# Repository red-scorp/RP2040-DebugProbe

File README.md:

```
____________  _____  _____    ___ _____                
| ___ \ ___ \/ __  \|  _  |  /   |  _  |               
| |_/ / |_/ /`' / /'| |/' | / /| | |/' |               
|    /|  __/   / /  |  /| |/ /_| |  /| |               
| |\ \| |    ./ /___\ |_/ /\___  \ |_/ /               
\_| \_\_|    \_____/ \___/     |_/\___/                
______     _                ______          _          
|  _  \   | |               | ___ \        | |         
| | | |___| |__  _   _  __ _| |_/ / __ ___ | |__   ___ 
| | | / _ \ '_ \| | | |/ _` |  __/ '__/ _ \| '_ \ / _ \
| |/ /  __/ |_) | |_| | (_| | |  | | | (_) | |_) |  __/
|___/ \___|_.__/ \__,_|\__, \_|  |_|  \___/|_.__/ \___|
                        __/ |                          
                       |___/                           
```

# RP2040-DebugProbe Project

The **RP2040-DebugProbe** project aims to re-imagine Raspberry Pi Debug Probe.

## RP2040-DebugProbe Board

The **RP2040-DebugProbe** board is a 4-layer design intended to accommodate the popular Raspberry Pi RP2040 MCU with all required component to function identically to Raspberry Pi Debug Probe.

This board features target JTAG connector and PC host USB Type-C connector. It also has a SWD connector and UART connector for the main MCU debugging. The board is pin-compatible with Raspberry Pi Debug Probe and can be used with the same picoprobe SW.

Preview:

You can view the [Schematics in PDF format](doc/RP2040-DebugProbe.pdf) for detailed information.

STEP 3D file is available [with pins](doc/RP2040-DebugProbe.step).

Features:

- Very small form-factor of about 50x25mm (2x1in).
- Raspberry Pi RP2040 MCU as a heart of the board.
- 2x5 1.27mm JTAG connector for programming and debugging.
- 1x8 2.54mm SWD/UART/Power connector for programming and debugging.
- USB Type-C connector for power and communication.
- Several LEDs to indicate power and status.
- 2x5 1.27mm SWD connector and 1x3 2.54mm UART connector for main MCU debugging.
- BOOTSEL button to enter the bootloader mode for flashing new picoprobe SW.
- Pin-compatible with Raspberry Pi Debug Probe.
- Extra TARGET_RESET line connected to GPIO10 for target MCU reset over JTAG.

CAM files, as well as the BOM and CPL files for JLCPCB, are available.

## Version History

### v1.0b1

Initial release for testing purposes.

## Links

- [Raspberry Pi RP2040 information page](https://www.raspberrypi.com/documentation/microcontrollers/rp2040.html).
- [Raspberry Pi Debug Probe information page](https://www.raspberrypi.com/documentation/microcontrollers/debug-probe.html).
- [Picoprobe SW for the board](https://github.com/raspberrypi/picoprobe).

## How to Help

Your contributions as code, resources, or finances are welcome! Please contact me directly via email at andriy.golovnya@gmail.com or through my [GitHub profile](https://github.com/red-scorp).

If you'd like to make a financial contribution, you can donate via [PayPal](http://paypal.me/redscorp) or [Ko-Fi](http://ko-fi.com/redscorp). Your support is greatly appreciated.

Thanks in advance!

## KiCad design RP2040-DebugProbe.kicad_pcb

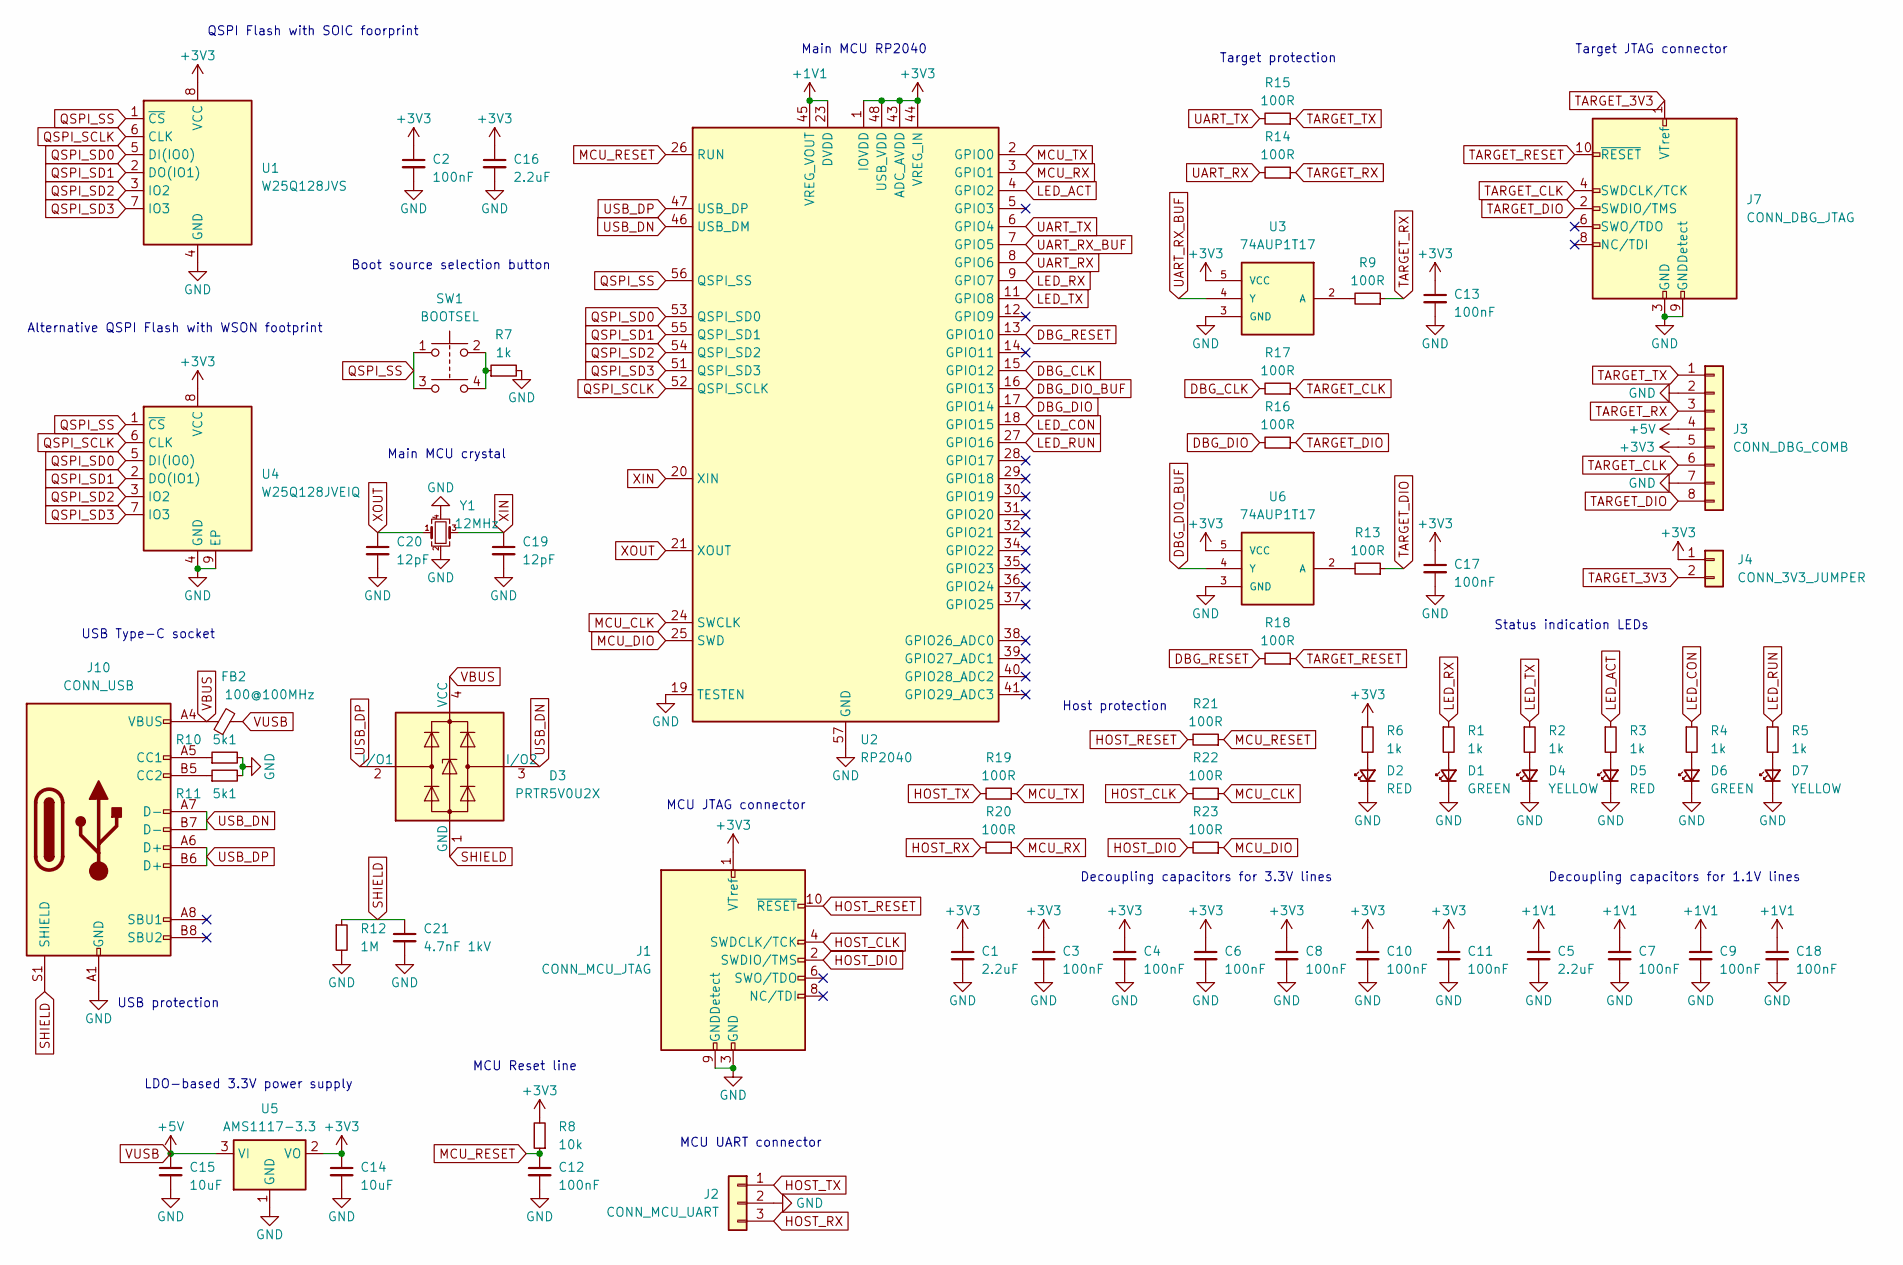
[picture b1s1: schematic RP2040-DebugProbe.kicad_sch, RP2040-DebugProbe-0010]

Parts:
C1, C5, C16: 2.2uF; C_0603_1608Metric
C2, C3, C4, C6, C7, C8, C9, C10, C11, C12, C13, C17, C18: 100nF; C_0402_1005Metric
C14, C15: 10uF; C_0805_2012Metric
C19, C20: 12pF; C_0402_1005Metric
C21: 4.7nF 1kV; C_1206_3216Metric
D1, D6: GREEN; LED_0603_1608Metric
D2, D5: RED; LED_0603_1608Metric
D3: PRTR5V0U2X; SOT-143
D4, D7: YELLOW; LED_0603_1608Metric
FB2: 100@100MHz; L_0805_2012Metric
J1: CONN_MCU_JTAG; PinHeader_2x05_P1.27mm_Vertical
J2: CONN_MCU_UART; PinHeader_1x03_P2.54mm_Vertical
J3: CONN_DBG_COMB; PinHeader_1x08_P2.54mm_Vertical
J4: CONN_3V3_JUMPER; PinHeader_1x02_P2.54mm_Vertical
J7: CONN_DBG_JTAG; PinHeader_2x05_P1.27mm_Vertical
J10: CONN_USB; USB_C_Receptacle_HRO_TYPE-C-31-M-12
R1, R2, R3, R4, R5, R6, R7: 1k; R_0402_1005Metric
R8: 10k; R_0402_1005Metric
R9, R13, R14, R15, R16, R17, R18, R19, R20, R21, R22, R23: 100R; R_0402_1005Metric
R10, R11: 5k1; R_0402_1005Metric
R12: 1M; R_0603_1608Metric
SW1: BOOTSEL; Button_Tact_Sqkg
U1: W25Q128JVS; SOIC-8_5.23x5.23mm_P1.27mm
U2: RP2040; QFN-56-1EP_7x7mm_P0.4mm_EP3.2x3.2mm
U3, U6: 74AUP1T17; SOT-353_SC-70-5
U4: W25Q128JVEIQ; WSON-8-1EP_6x5mm_P1.27mm_EP3.4x4.3mm
U5: AMS1117-3.3; SOT-223-3_TabPin2
Y1: 12MHz; Crystal_SMD_3225-4Pin_3.2x2.5mm

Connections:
+1V1: C5.1, C7.1, C9.1, C18.1, U2.23 (DVDD), U2.45 (VREG_VOUT), U2.50 (DVDD)
+3V3: C1.1, C2.1, C3.1, C4.1, C6.1, C8.1, C10.1, C11.1, C13.1, C14.1, C16.1, C17.1, J1.1 (VTref), J3.5, J4.1, R6.1, R8.2, U1.8 (VCC), U2.1 (IOVDD), U2.10 (IOVDD), U2.22 (IOVDD), U2.33 (IOVDD), U2.42 (IOVDD), U2.43 (ADC_AVDD), U2.44 (VREG_IN), U2.48 (USB_VDD), U2.49 (IOVDD), U3.5 (VCC), U4.8 (VCC), U5.2 (VO), U6.5 (VCC)
DBG_CLK: R17.2, U2.15 (GPIO12)
DBG_DIO: R16.2, U2.17 (GPIO14)
DBG_DIO_BUF: U2.16 (GPIO13), U6.4 (Y)
DBG_RESET: R18.2, U2.13 (GPIO10)
GND: C1.2, C2.2, C3.2, C4.2, C5.2, C6.2, C7.2, C8.2, C9.2, C10.2, C11.2, C12.2, C13.2, C14.2, C15.2, C16.2, C17.2, C18.2, C19.2, C20.2, C21.2, D1.1 (K), D2.1 (K), D4.1 (K), D5.1 (K), D6.1 (K), D7.1 (K), J1.3 (GND), J1.5 (GND), J1.9 (GNDDetect), J2.2, J3.2, J3.7, J7.3 (GND), J7.5 (GND), J7.9 (GNDDetect), J10.A1 (GND), J10.A12 (GND), J10.B1 (GND), J10.B12 (GND), R7.2, R10.2, R11.2, R12.2, U1.4 (GND), U2.19 (TESTEN), U2.57 (GND), U3.3 (GND), U4.4 (GND), U4.9 (EP), U5.1 (GND), U6.3 (GND), Y1.2, Y1.4
HOST_CLK: J1.4 (SWDCLK/TCK), R22.2
HOST_DIO: J1.2 (SWDIO/TMS), R23.2
HOST_RESET: J1.10 (~RESET), R21.2
HOST_RX: J2.3, R20.2
HOST_TX: J2.1, R19.2
LED_ACT: R3.1, U2.4 (GPIO2)
LED_CON: R4.1, U2.18 (GPIO15)
LED_RUN: R5.1, U2.27 (GPIO16)
LED_RX: R1.1, U2.9 (GPIO7)
LED_TX: R2.1, U2.11 (GPIO8)
MCU_CLK: R22.1, U2.24 (SWCLK)
MCU_DIO: R23.1, U2.25 (SWD)
MCU_RESET: C12.1, R8.1, R21.1, U2.26 (RUN)
MCU_RX: R20.1, U2.3 (GPIO1)
MCU_TX: R19.1, U2.2 (GPIO0)
unnamed: D1.2 (A), R1.2
unnamed: D2.2 (A), R6.2
unnamed: D4.2 (A), R2.2
unnamed: D5.2 (A), R3.2
unnamed: D6.2 (A), R4.2
unnamed: D7.2 (A), R5.2
unnamed: J10.A5 (CC1), R10.1
unnamed: J10.B5 (CC2), R11.1
unnamed: R7.1, SW1.2, SW1.4
unnamed: R9.2, U3.2 (A)
unnamed: R13.2, U6.2 (A)
QSPI_SCLK: U1.6 (CLK), U2.52 (QSPI_SCLK), U4.6 (CLK)
QSPI_SD0: U1.5 (DI(IO0)), U2.53 (QSPI_SD0), U4.5 (DI(IO0))
QSPI_SD1: U1.2 (DO(IO1)), U2.55 (QSPI_SD1), U4.2 (DO(IO1))
QSPI_SD2: U1.3 (IO2), U2.54 (QSPI_SD2), U4.3 (IO2)
QSPI_SD3: U1.7 (IO3), U2.51 (QSPI_SD3), U4.7 (IO3)
QSPI_SS: SW1.1, SW1.3, U1.1 (~CS), U2.56 (QSPI_SS), U4.1 (~CS)
SHIELD: C21.1, D3.1 (GND), J10.S1 (SHIELD), R12.1
TARGET_3V3: J4.2, J7.1 (VTref)
TARGET_CLK: J3.6, J7.4 (SWDCLK/TCK), R17.1
TARGET_DIO: J3.8, J7.2 (SWDIO/TMS), R13.1, R16.1
TARGET_RESET: J7.10 (~RESET), R18.1
TARGET_RX: J3.3, R9.1, R14.1
TARGET_TX: J3.1, R15.1
UART_RX: R14.2, U2.8 (GPIO6)
UART_RX_BUF: U2.7 (GPIO5), U3.4 (Y)
UART_TX: R15.2, U2.6 (GPIO4)
USB_DN: D3.3 (I/O2), J10.A7 (D-), J10.B7 (D-), U2.46 (USB_DM)
USB_DP: D3.2 (I/O1), J10.A6 (D+), J10.B6 (D+), U2.47 (USB_DP)
VBUS: D3.4 (VCC), FB2.1, J10.A4 (VBUS), J10.A9 (VBUS), J10.B4 (VBUS), J10.B9 (VBUS)
VUSB: C15.1, FB2.2, J3.4, U5.3 (VI)
XIN: C19.1, U2.20 (XIN), Y1.3
XOUT: C20.1, U2.21 (XOUT), Y1.1

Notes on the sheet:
USB protection
Alternative QSPI Flash with WSON footprint
Main MCU RP2040
Status indication LEDs
MCU JTAG connector
Decoupling capacitors for 3.3V lines
Main MCU crystal
Decoupling capacitors for 1.1V lines
Target protection
Target JTAG connector
USB Type-C socket
Host protection
MCU UART connector
Boot source selection button
LDO-based 3.3V power supply
MCU Reset line
QSPI Flash with SOIC foorprint

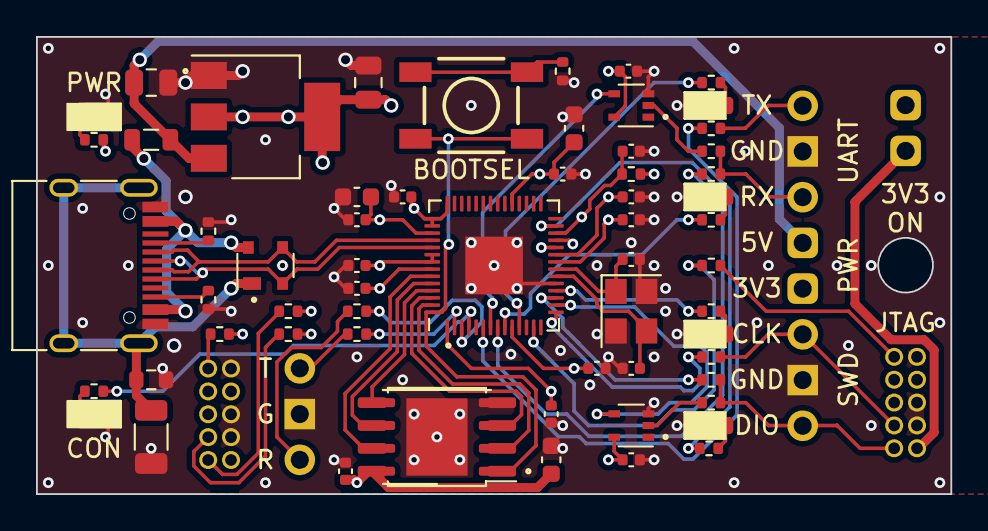
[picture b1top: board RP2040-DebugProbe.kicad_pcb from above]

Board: 4 copper layers, 50.8 x 25.4 mm, 66 parts (0 on the bottom side), 55 nets.

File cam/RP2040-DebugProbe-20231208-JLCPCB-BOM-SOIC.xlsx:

Qty | Designator | Footprint | JLCPCB Part# | Comment
12 | R13,R19,R23,R15,R16,R22,R18,R17,R21,R9,R20,R14 | 0402 | C25076 | 100R
2 | D7,D4 | 0603 | C72038 | YELLOW
13 | C4,C11,C9,C3,C17,C7,C12,C13,C18,C2,C6,C10,C8 | 0402 | C1525 | 100nF
3 | C5,C1,C16 | 0603 | C1604 | 2.2uF
1 | FB2 | 0805 | C1015 | GZ2012D101TF
2 | U3,U6 | SC-70-5 | C2652100 | 74AUP1T17
2 | D2,D5 | 0603 | C2286 | RED
2 | R11,R10 | 0402 | C25905 | 5k1
1 | J1 | SMD,P=1.27mm | C2935953 | CONN_MCU_JTAG
2 | C20,C19 | 0402 | C1547 | 12pF
1 | U2 | LQFN-56(7x7) | C2040 | RP2040
7 | R3,R7,R5,R1,R6,R4,R2 | 0402 | C11702 | 1k
1 | J4 | Plugin,P=2.54mm | C2685154 | CONN_3V3_JUMPER
1 | C21 | 1206 | C106074 | 4.7nF 1kV
2 | C14,C15 | 0805 | C15850 | 10uF
1 | J7 | SMD,P=1.27mm | C2935953 | CONN_DBG_JTAG
1 | D3 | SOT-143 | C5158049 | PRTR5V0U2X
1 | SW1 | SMD | C318884 | TS-1187A-B-A-B
2 | D1,D6 | 0603 | C72043 | GREEN
1 | J10 | SMD | C2689844 | CONN_USB
1 | Y1 | SMD3225-4P | C9002 | 12MHz
1 | U1 | SOIC-8-208mil | C97521 | W25Q128JVS
1 | U5 | SOT-223 | C6187 | AMS1117-3.3
1 | J3 | Plugin,P=2.54mm | C6332201 | CONN_DBG_COMB
1 | J2 | Plugin,P=2.54mm | C429954 | CONN_MCU_UART
1 | R8 | 0402 | C25744 | 10k
1 | R12 | 0603 | C136593 | 1M

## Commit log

2023-12-03 Created base schematics based on current RP2040-Eins board
2023-12-03 Added buffer chip
2023-12-03 Improved schematics
2023-12-03 Added basic board layout
2023-12-04 Placed components on their approximate locations. Added board approximate outline.
2023-12-04 Moved stuff around
2023-12-05 Added 3D models to the board components
2023-12-06 Made the board 4 layer. Made a basic routing.
2023-12-07 Generated PDF schematics
2023-12-07 Added target reset line on GPIO 10
2023-12-07 Added host side protection resistors
2023-12-07 Added README.md with initial information.
2023-12-08 Updated file export parameters
2023-12-08 Generated CAM files
2023-12-10 Generated generic BOM and CPL files
2023-12-10 Added center lines for connectors
2023-12-10 Generated BOM and CPL files
2023-12-10 Generated STEP 3D model
2023-12-10 Generated PNG preview
2023-12-10 Removed TODO label
2023-12-10 Added FUNDING.yml file
2023-12-14 Added banner text into README file
2023-12-24 Moved misplaced label

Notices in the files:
RP2040-DebugProbe.kicad_pcb:
(c) 2023 Andriy Golovnya
